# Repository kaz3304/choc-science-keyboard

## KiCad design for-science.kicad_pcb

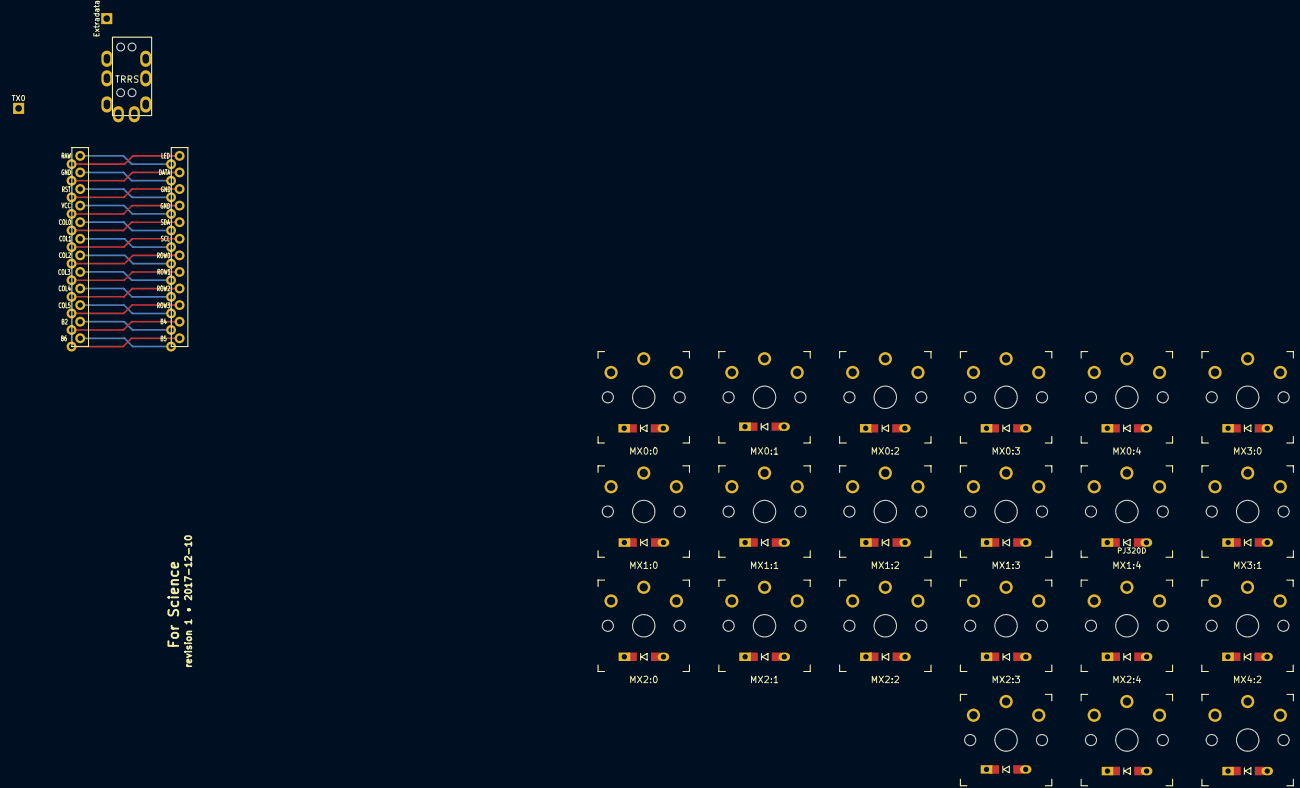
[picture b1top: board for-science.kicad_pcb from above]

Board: 2 copper layers, 50 parts (0 on the bottom side), 36 nets.

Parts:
D1, D2, D3, D4, D5, D7, D8, D9, D10, D11, D13, D14, D15, D16, D17, D19, D20, D21, D22, D23, D26: DIODE; D3_TH_SMD_v2
EXTRADATA1: Extradata; PIN_1_SQUARE
J*: MJ-4PP-9
M8, M8#2, M8#3, M8#4: MountingHole_8.4mm_M8
MX0:0: MX0:9; SW_PG1350_reversible_nohole
MX0:1: MX0:8; SW_PG1350_reversible_nohole
MX0:2: MX0:7; SW_PG1350_reversible_nohole
MX0:3: MX0:6; SW_PG1350_reversible_nohole
MX0:4: MX0:5; SW_PG1350_reversible_nohole
MX1:0: MX1:9; SW_PG1350_reversible_nohole
MX1:1: MX1:8; SW_PG1350_reversible_nohole
MX1:2, MX1:4: MX1:7; SW_PG1350_reversible_nohole
MX1:3: MX1:6; SW_PG1350_reversible_nohole
MX2:0: MX2:9; SW_PG1350_reversible_nohole
MX2:1: MX2:8; SW_PG1350_reversible_nohole
MX2:2: MX2:7; SW_PG1350_reversible_nohole
MX2:3: MX2:6; SW_PG1350_reversible_nohole
MX2:4: MX2:5; SW_PG1350_reversible_nohole
MX3:0: MX3:9; SW_PG1350_reversible_nohole
MX3:1: MX3:8; SW_PG1350_reversible_nohole
MX3:2: MX3:7; SW_PG1350_reversible_nohole
MX3:3: MX3:6; SW_PG1350_reversible_nohole
MX3:4: MX3:5; SW_PG1350_reversible_nohole
MX4:2: MX4:7; SW_PG1350_reversible_nohole
TX0: TX0; PIN_1_SQUARE
U1: ProMicro; ProMicro_v2

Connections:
/Col0: MX0:0.1, MX1:0.1, MX2:0.1, MX3:0.1, U1.18
/Col1: MX0:1.1, MX1:1.1, MX2:1.1, MX3:1.1, U1.17
/Col2: MX0:2.1, MX1:2.1, MX2:2.1, MX3:2.1, MX4:2.1, U1.16
/Col3: MX0:3.1, MX1:3.1, MX2:3.1, MX3:3.1, U1.15
/Col4: MX0:4.1, MX1:4.1, MX2:4.1, MX3:4.1, U1.14
/Row0: D1.2, D2.2, D3.2, D4.2, D5.2, U1.7
/Row1: D7.2, D8.2, D9.2, D10.2, D11.2, U1.9
/Row2: D13.2, D14.2, D15.2, D16.2, D17.2, U1.10
/Row3: D19.2, D20.2, D21.2, D22.2, D23.2, U1.11
/Row4: D26.2, U1.12
GND: J*.4, U1.4
unnamed: D1.1, MX0:0.2
unnamed: D2.1, MX0:1.2
unnamed: D3.1, MX0:2.2
unnamed: D4.1, MX0:3.2
unnamed: D5.1, MX0:4.2
unnamed: D7.1, MX1:0.2
unnamed: D8.1, MX1:1.2
unnamed: D9.1, MX1:2.2
unnamed: D10.1, MX1:3.2
unnamed: D11.1, MX1:4.2
unnamed: D13.1, MX2:0.2
unnamed: D14.1, MX2:1.2
unnamed: D15.1, MX2:2.2
unnamed: D16.1, MX2:3.2
unnamed: D17.1, MX2:4.2
unnamed: D19.1, MX3:0.2
unnamed: D20.1, MX3:1.2
unnamed: D21.1, MX3:2.2
unnamed: D22.1, MX3:3.2
unnamed: D23.1, MX3:4.2
unnamed: D26.1, MX4:2.2
unnamed: EXTRADATA1.1, J*.3
unnamed: J*.1, U1.6
unnamed: TX0.1, U1.1
VCC: J*.2, U1.21

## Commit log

2021-12-26 initial attempts
